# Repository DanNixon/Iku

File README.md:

Iku
===

A kit that converts a standard ATX PS2 power suppy into a bench power supply.

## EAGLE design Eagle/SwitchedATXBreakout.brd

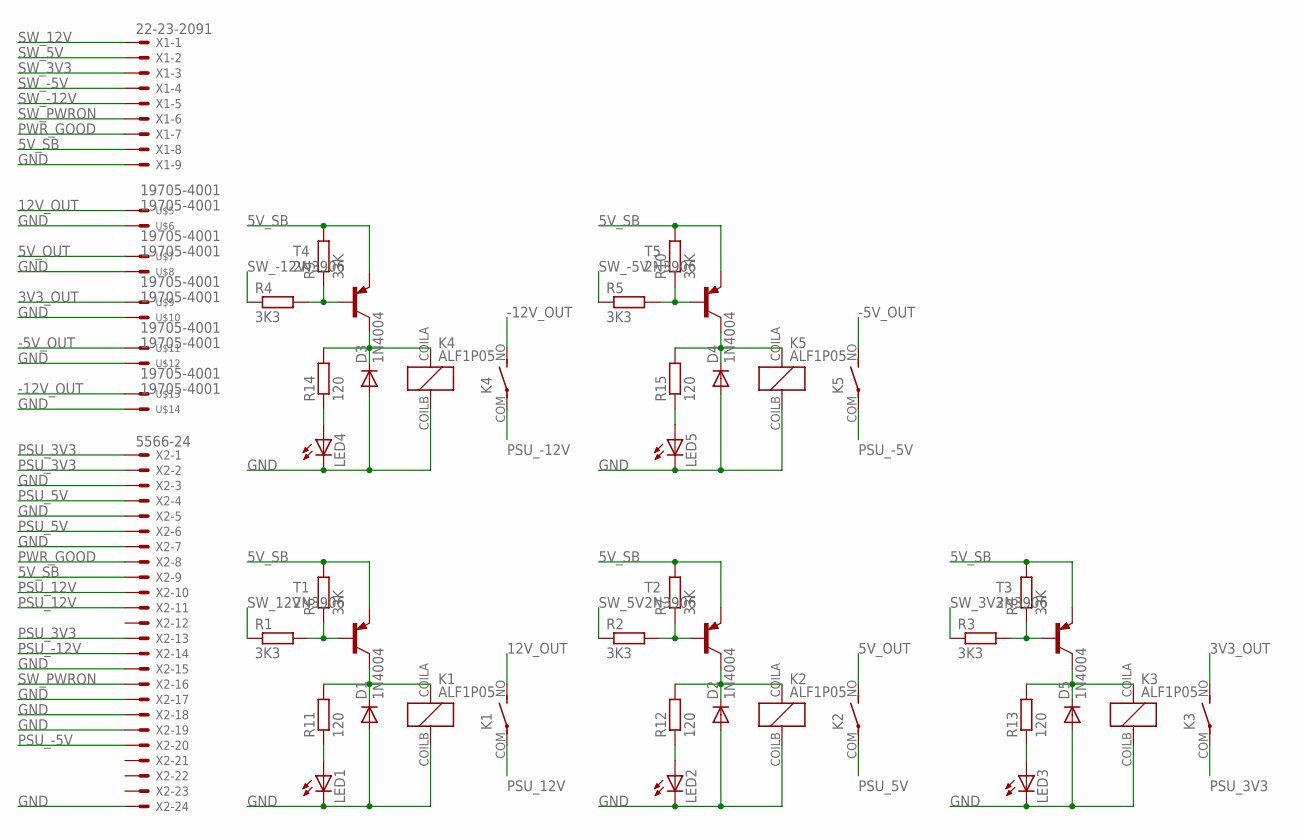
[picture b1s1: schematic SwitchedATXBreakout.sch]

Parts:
D1, D2, D3, D4, D5: 1N4004; DO41-10
K1, K2, K3, K4, K5: ALF1P05; ALF
LED1, LED2, LED3, LED4, LED5: LED3MM
R1, R2, R3, R4, R5: 3K3; 0204/7
R6, R7, R8, R9, R10: 33K; 0204/7
R11, R12, R13, R14, R15: 120; 0204/7
T1, T2, T3, T4, T5: 2N3906; TO92-EBC
U$5, U$6, U$7, U$8, U$9, U$10, U$11, U$12, U$13, U$14: 19705-4001
X1: 22-23-2091
X2: 5566-24

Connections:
3V3_OUT: K3.NO (S), U$9.P$1, U$9.P$2
5V_OUT: K2.NO (S), U$7.P$1, U$7.P$2
5V_SB: R6.2, R7.2, R8.2, R9.2, R10.2, T1.E, T2.E, T3.E, T4.E, T5.E, X1.8, X2.9
12V_OUT: K1.NO (S), U$5.P$1, U$5.P$2
-5V_OUT: K5.NO (S), U$11.P$1, U$11.P$2
-12V_OUT: K4.NO (S), U$13.P$1, U$13.P$2
GND: D1.A, D2.A, D3.A, D4.A, D5.A, K1.COILB (2), K2.COILB (2), K3.COILB (2), K4.COILB (2), K5.COILB (2), LED1.K (C), LED2.K (C), LED3.K (C), LED4.K (C), LED5.K (C), U$6.P$1, U$6.P$2, U$8.P$1, U$8.P$2, U$10.P$1, U$10.P$2, U$12.P$1, U$12.P$2, U$14.P$1, U$14.P$2, X1.9, X2.3, X2.5, X2.7, X2.15, X2.17, X2.18, X2.19, X2.24
unnamed: R1.2, R6.1, T1.B
unnamed: R4.2, R9.1, T4.B
unnamed: D1.C, K1.COILA (1), R11.2, T1.C
unnamed: D2.C, K2.COILA (1), R12.2, T2.C
unnamed: R5.2, R10.1, T5.B
unnamed: R2.2, R7.1, T2.B
unnamed: R3.2, R8.1, T3.B
unnamed: D3.C, K4.COILA (1), R14.2, T4.C
unnamed: LED1.A, R11.1
unnamed: LED2.A, R12.1
unnamed: D4.C, K5.COILA (1), R15.2, T5.C
unnamed: LED3.A, R13.1
unnamed: LED5.A, R15.1
unnamed: D5.C, K3.COILA (1), R13.2, T3.C
unnamed: LED4.A, R14.1
PSU_3V3: K3.COM, X2.1, X2.2, X2.13
PSU_5V: K2.COM, X2.4, X2.6
PSU_12V: K1.COM, X2.10, X2.11
PSU_-5V: K5.COM, X2.20
PSU_-12V: K4.COM, X2.14
PWR_GOOD: X1.7, X2.8
SW_3V3: R3.1, X1.3
SW_5V: R2.1, X1.2
SW_12V: R1.1, X1.1
SW_-5V: R5.1, X1.4
SW_-12V: R4.1, X1.5
SW_PWRON: X1.6, X2.16

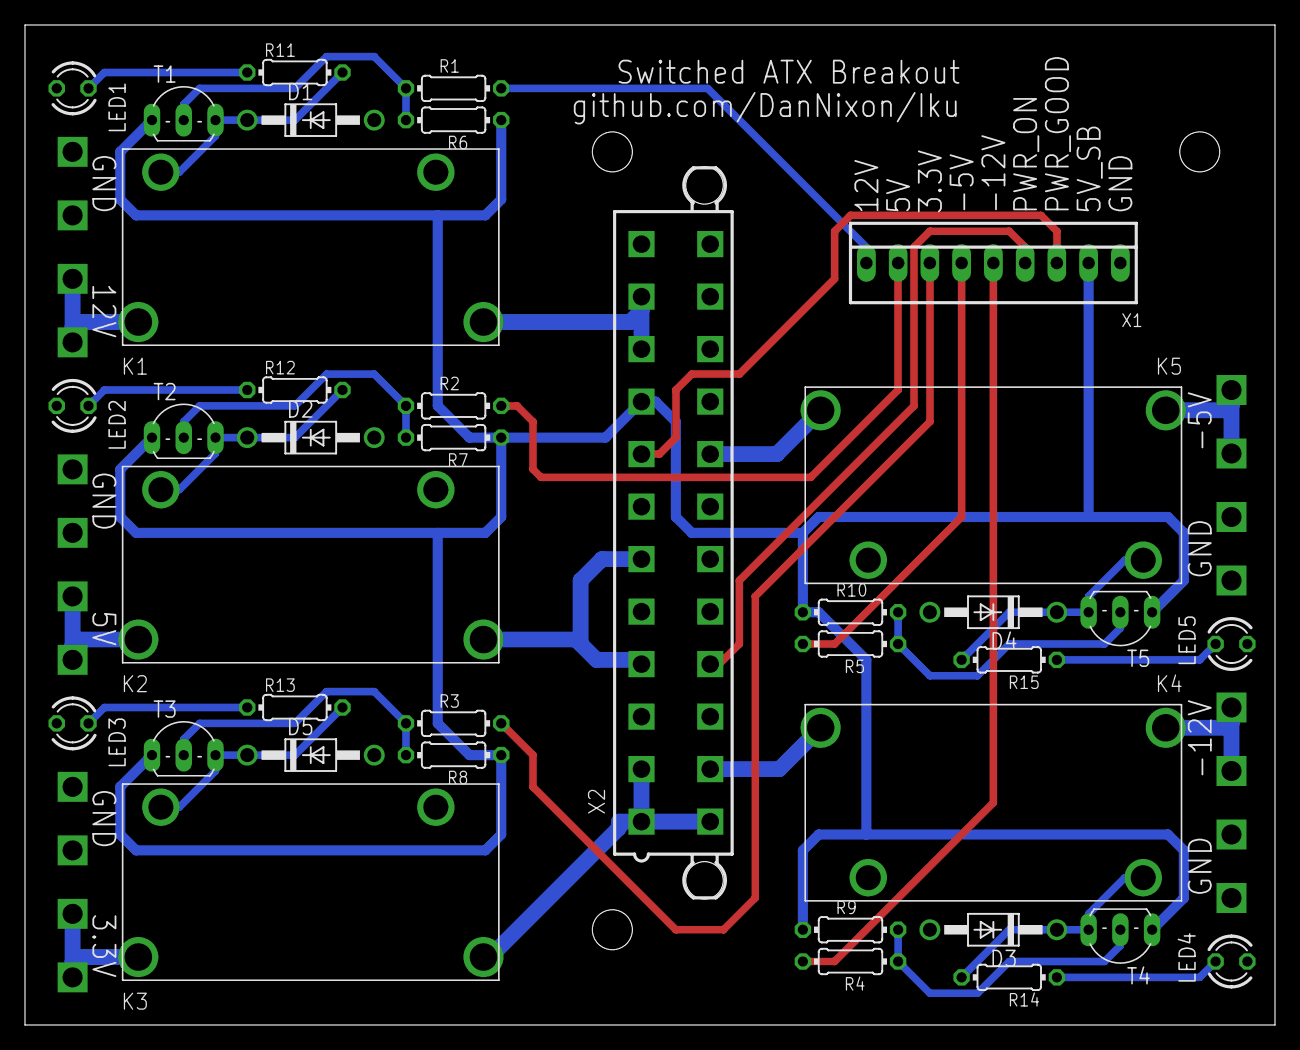
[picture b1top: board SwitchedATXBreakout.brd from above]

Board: 2 copper layers, 100.0 x 80.0 mm, 47 parts (0 on the bottom side), 34 nets.

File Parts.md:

Parts
=====

List of parts that can be purchased from Mouser:

- [ATX power connector (Molex)](http://uk.mouser.com/ProductDetail/Molex/39-28-1243/?qs=%2fh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
- [Screw terminals](http://uk.mouser.com/ProductDetail/Pomona-Electronics/6883/?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
- [Channel switches](http://uk.mouser.com/ProductDetail/NKK-Switches/CWSB11AA2F/?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
- [Main switch](http://uk.mouser.com/ProductDetail/NKK-Switches/M2033TNW01-E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
- [Relays](http://uk.mouser.com/ProductDetail/Panasonic/ALF1P05/?qs=%2f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
- [Spade terminals (Molex)](http://uk.mouser.com/ProductDetail/Molex/19705-4001/?qs=sGAE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
- [1N4007](http://uk.mouser.com/ProductDetail/Fairchild-Semiconductor/1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
- [2N3906](http://uk.mouser.com/ProductDetail/Central-Semiconductor/2N3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

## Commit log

2015-03-12 Initial CAD files
2015-03-12 Added front panel
2015-03-12 Updates, added tabs
2015-03-12 Lay out front panel
2015-03-14 Minor fixes for front panel
2015-03-16 Added EAGLE project
2015-03-24 Update Eagle drawings
2015-03-24 More work on board
2015-03-26 Finish schematic
2015-03-28 Dont VC the project file
2015-03-28 Start board layout
2015-03-29 Finish board layout
2015-04-04 Updated board layout
2015-04-07 Fixed some placement errors
2015-04-10 Add switched ATX breakout to back panel
2015-04-18 Small updates
2015-04-18 Update CAD
2015-04-20 CAD update
2015-04-20 Move board
2015-06-14 Add links to parts
